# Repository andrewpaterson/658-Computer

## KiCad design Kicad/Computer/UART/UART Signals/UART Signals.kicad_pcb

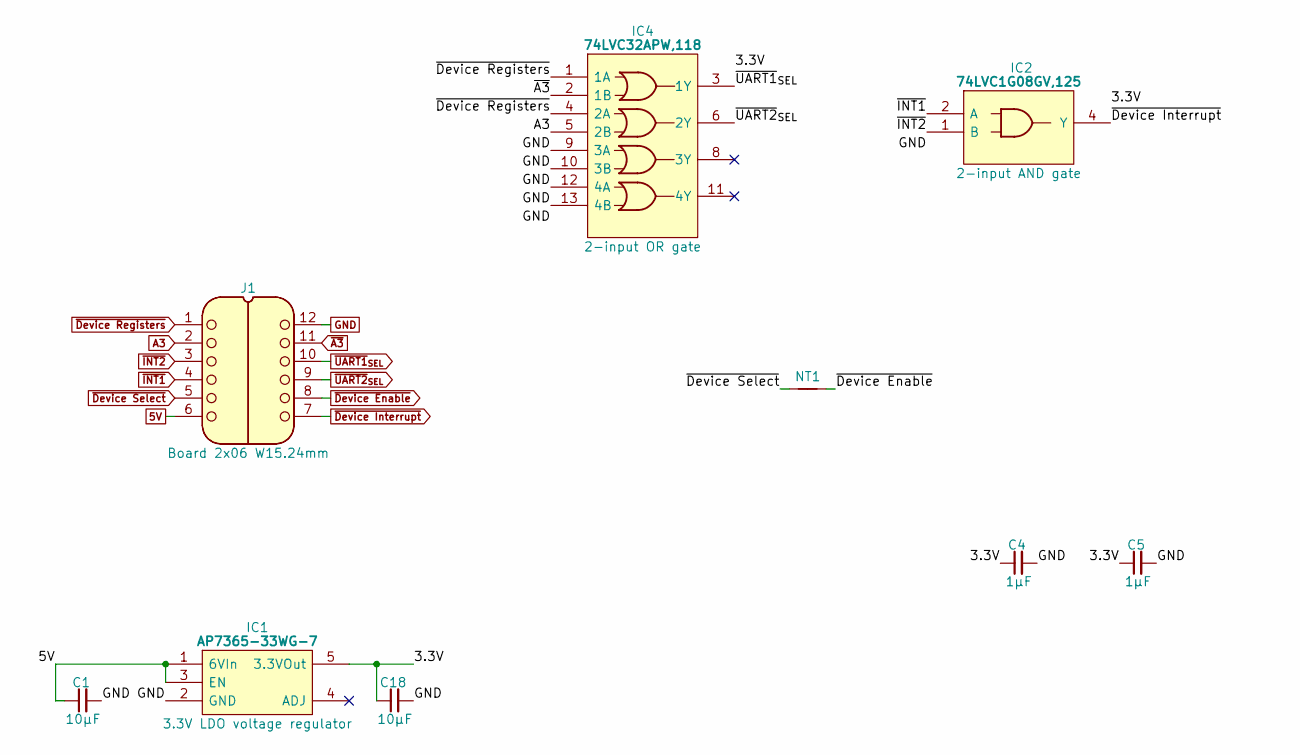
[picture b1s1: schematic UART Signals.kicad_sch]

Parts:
C1, C18: 10µF; C_0805
C4, C5: 1μF; C_0805
IC1: AP7365-33WG-7; SOT95P285X130-5N; Manufacturer_Part_Number AP7365-33WG-7; Mouser Part Number 621-AP7365-33WG-7
IC2: 74LVC1G08GV,125; SOT95P275X110-5N; Manufacturer_Part_Number 74LVC1G08GV,125; Mouser Part Number 771-74LVC1G08GV
IC4: 74LVC32APW,118; SOP65P640X110-14N; Manufacturer_Part_Number 74LVC32APW,118; Mouser Part Number 771-74LVC32APW-T
J1: Board 2x06 W15.24mm; DIP-12_Board_W15.24mm_Alt
NT1: NetTie; NetTie-2_SMD_Pad0.5mm

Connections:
5V: C1.1, IC1.1 (6VIn), IC1.3 (EN), J1.6
/3.3V: C4.1, C5.1, C18.1, IC1.5 (3.3VOut), IC2.5 (3V), IC4.14 (3V)
A3: IC4.5 (2B), J1.2
GND: C1.2, C4.2, C5.2, C18.2, IC1.2 (GND), IC2.3 (GND), IC4.7 (GND), IC4.9 (3A), IC4.10 (3B), IC4.12 (4A), IC4.13 (4B), J1.12
~A3: IC4.2 (1B), J1.11
~Device Enable: J1.8, NT1.2
~Device Interrupt: IC2.4 (Y), J1.7
~Device Registers: IC4.1 (1A), IC4.4 (2A), J1.1
~Device Select: J1.5, NT1.1
~INT1: IC2.2 (A), J1.4
~INT2: IC2.1 (B), J1.3
~UART1_{SEL}: IC4.3 (1Y), J1.10
~UART2_{SEL}: IC4.6 (2Y), J1.9

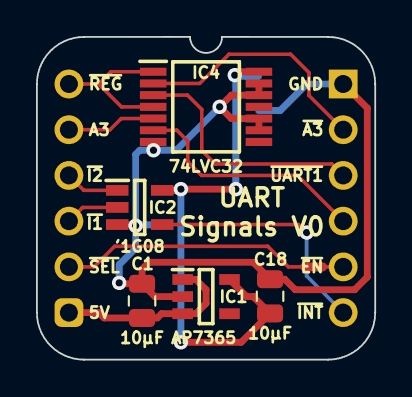
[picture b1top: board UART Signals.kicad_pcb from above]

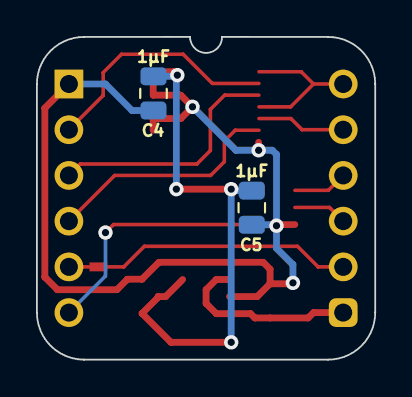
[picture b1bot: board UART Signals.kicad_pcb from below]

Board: 2 copper layers, 18.8 x 17.9 mm, 9 parts (2 on the bottom side), 13 nets.

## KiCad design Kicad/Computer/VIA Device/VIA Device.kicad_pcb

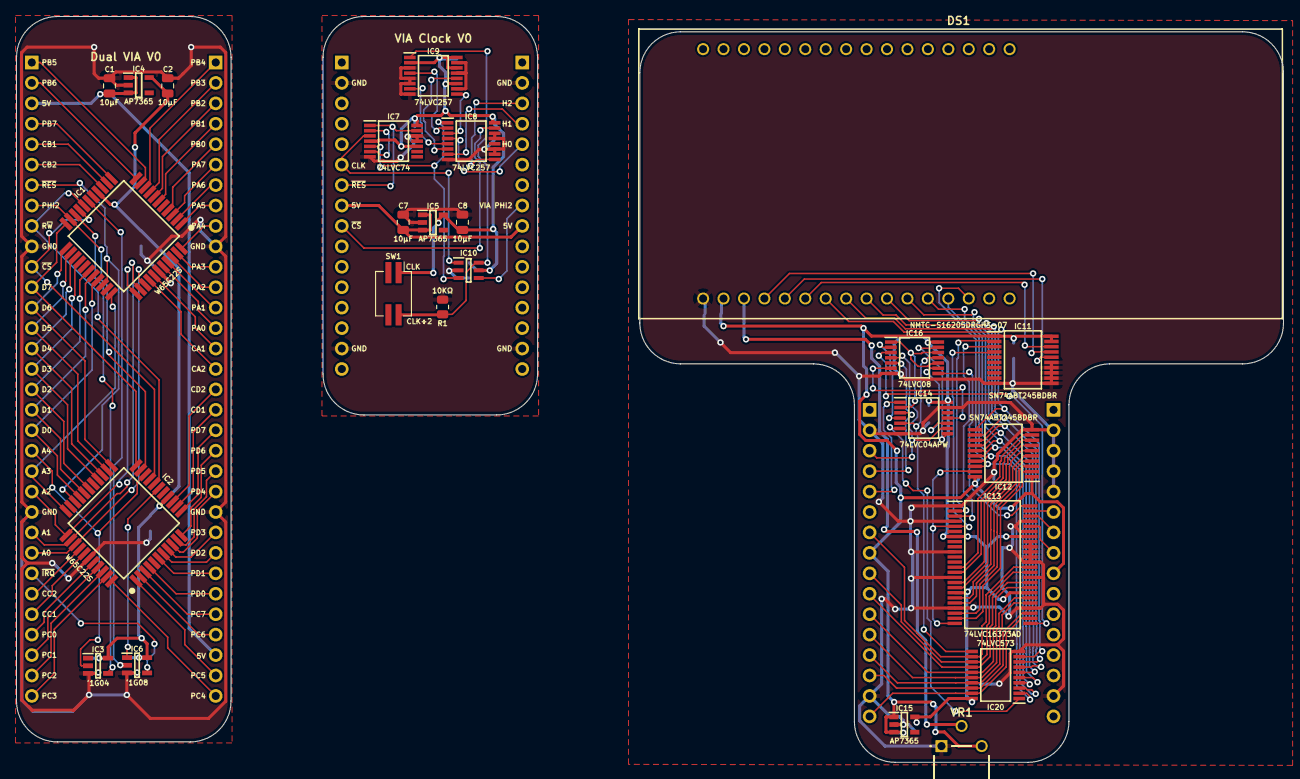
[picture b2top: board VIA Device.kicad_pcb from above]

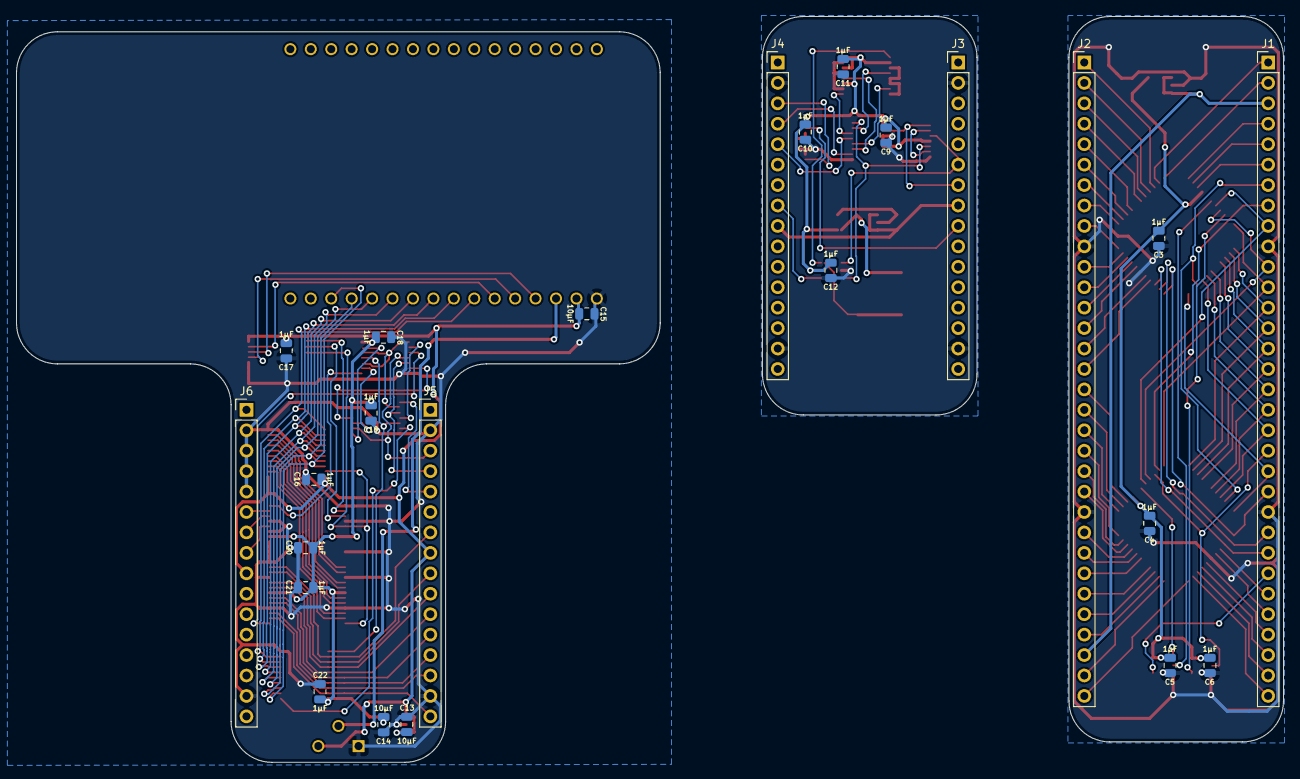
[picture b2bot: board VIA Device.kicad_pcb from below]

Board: 2 copper layers, 157.5 x 92.7 mm, 49 parts (24 on the bottom side), 130 nets.

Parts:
C1, C2, C7, C8, C13, C14, C15: 10μF; C_0805
C3, C4, C5, C6, C9, C10, C11, C12, C16, C17, C18, C19, C20, C21, C22: 1μF; C_0805
DS1: NMTC-S16205DRGHS-07; NMTCS16205DRGHS07_1
IC1, IC2: W65C22S6TQG-14; QFP80P1320X1320X270-44N
IC3: 74LVC1G04GV,125; SOT95P275X110-5N
IC4, IC5, IC15: AP7365-33WG-7; SOT95P285X130-5N
IC6: 74LVC1G08GV,125; SOT95P275X110-5N
IC7: 74LVC74APW,118; SOP65P640X110-14N
IC8, IC9: 74LVC257APW,118; SOP65P640X110-16N
IC10: 74LVC1G157GV-Q100H; SOT95P275X110-6N
IC11, IC12: SN74ABT245BDBR; SOP65P780X200-20N
IC13: 74LVC16373ADL,118; SOP64P1025X280-48N
IC14: 74LVC04APW,118; SOP65P640X110-14N
IC16: 74LVC08APW,112; SOP65P640X110-14N
IC20: 74LVC573APW,118; SOP65P640X110-20N
J1, J2: Conn_01x32_Pin; PinHeader_1x32_P2.54mm_Vertical
J3, J4, J5, J6: Conn_01x32_Pin; PinHeader_1x16_P2.54mm_Vertical
R1: 10KΩ; R_0805
SW1: SW_DIP_x02; SW_DIP_SPSTx02_Slide_KingTek_DSHP02TJ_W5.25mm_P1.27mm_JPin
VR1: 3306K-1-103; 3306K1103

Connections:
/Clock Control Board/1~Q: IC7.2 (1D), IC7.6 (~1Q)
/Clock Control Board/3.3V: C8.1, C9.1, C10.1, C11.1, C12.1, IC5.5 (VOUT), IC7.4 (~1SD), IC7.10 (~2SD), IC7.14 (3V), IC8.16 (3V), IC9.2 (1I0), IC9.11 (3I0), IC9.14 (4I0), IC9.16 (3V), IC10.5 (3V), SW1.1
/Clock Control Board/5V: C7.1, IC5.1 (VIN), IC5.3 (EN), J3.8, J4.9
/Clock Control Board/CH0_{OUT}: IC8.4 (1Y), J4.5
/Clock Control Board/CH1_{OUT}: IC8.7 (2Y), J4.4
/Clock Control Board/CH2_{OUT}: IC8.9 (3Y), J4.3
/Clock Control Board/CLK: IC7.3 (1CP), IC10.1 (I1), J3.6
/Clock Control Board/CLK÷2: IC7.5 (1Q), IC8.1 (S), IC10.3 (I0)
/Clock Control Board/GND: C7.2, C8.2, C9.2, C10.2, C11.2, C12.2, IC5.2 (GND), IC7.7 (GND), IC7.11 (2CP), IC7.12 (2D), IC8.8 (GND), IC8.10 (3I1), IC8.11 (3I0), IC8.13 (4I1), IC8.14 (4I0), IC9.3 (1I1), IC9.5 (2I0), IC9.6 (2I1), IC9.8 (GND), IC9.10 (3I1), IC9.13 (4I1), IC9.15 (~OE), IC10.2 (GND), J3.2, J3.15, J4.2, J4.15, R1.1
/Clock Control Board/Select CLK÷2: IC9.1 (S), IC10.6 (S), R1.2, SW1.4
/Clock Control Board/VIA PHI2 _{OUT}: IC10.4 (Y), J4.8
/Clock Control Board/~CS: IC8.15 (~OE), J3.9
/Clock Control Board/~Reset: IC7.1 (~1RD), IC7.13 (~2RD), J3.7
/LCD Display/3.3V: C14.1, C18.1, C19.1, C20.1, C21.1, C22.1, IC13.7 (3V), IC13.18 (3V), IC13.31 (3V), IC13.42 (3V), IC14.14 (3V), IC15.5 (VOUT), IC16.14 (3V), IC20.20 (3V)
/LCD Display/5V: C13.1, C15.1, C16.1, C17.1, DS1.2 (5V), IC11.1 (DIR), IC11.19 (~OE), IC11.20 (5V), IC12.1 (DIR), IC12.20 (5V), IC15.1 (VIN), IC15.3 (EN), J5.8, J6.9, VR1.3 (VIN)
/LCD Display/(RD+WD)·CS: IC13.48 (1LE), IC16.8 (3Y)
/LCD Display/A0: IC13.37 (1D7), J6.6
/LCD Display/A1: IC13.38 (1D6), J6.7
/LCD Display/A2: IC13.40 (1D5), J6.8
/LCD Display/CS: IC14.2 (1Y), IC16.1 (1A), IC16.10 (3B), IC16.12 (4A)
/LCD Display/D0: IC13.26 (2D7), IC20.12 (Q7), J5.7
/LCD Display/D0_{Latch}: IC12.2 (A0), IC13.23 (2Q7)
/LCD Display/D1: IC13.27 (2D6), IC20.13 (Q6), J5.9
/LCD Display/D1_{Latch}: IC12.3 (A1), IC13.22 (2Q6)
/LCD Display/D2: IC13.29 (2D5), IC20.14 (Q5), J5.10
/LCD Display/D2_{Latch}: IC12.4 (A2), IC13.20 (2Q5)
/LCD Display/D3: IC13.30 (2D4), IC20.15 (Q4), J5.11
/LCD Display/D3_{Latch}: IC12.5 (A3), IC13.19 (2Q4)
/LCD Display/D4: IC13.32 (2D3), IC20.16 (Q3), J5.12
/LCD Display/D4_{Latch}: IC12.6 (A4), IC13.17 (2Q3)
/LCD Display/D5: IC13.33 (2D2), IC20.17 (Q2), J5.13
/LCD Display/D5_{Latch}: IC12.7 (A5), IC13.16 (2Q2)
/LCD Display/D6: IC13.35 (2D1), IC20.18 (Q1), J5.14
/LCD Display/D6_{Latch}: IC12.8 (A6), IC13.14 (2Q1)
/LCD Display/D7: IC13.36 (2D0), IC20.19 (Q0), J5.16
/LCD Display/D7_{Latch}: IC12.9 (A7), IC13.13 (2Q0)
/LCD Display/DB0: DS1.7 (DB0), IC12.18 (B0), IC20.9 (D7)
/LCD Display/DB1: DS1.8 (DB1), IC12.17 (B1), IC20.8 (D6)
/LCD Display/DB2: DS1.9 (DB2), IC12.16 (B2), IC20.7 (D5)
/LCD Display/DB3: DS1.10 (DB3), IC12.15 (B3), IC20.6 (D4)
/LCD Display/DB4: DS1.11 (DB4), IC12.14 (B4), IC20.5 (D3)
/LCD Display/DB5: DS1.12 (DB5), IC12.13 (B5), IC20.4 (D2)
/LCD Display/DB6: DS1.13 (DB6), IC12.12 (B6), IC20.3 (D1)
/LCD Display/DB7: DS1.14 (DB7), IC12.11 (B7), IC20.2 (D0)
/LCD Display/E: DS1.6 (E), IC11.11 (B7)
/LCD Display/E_{Latch}: IC11.9 (A7), IC13.12 (1Q7)
/LCD Display/GND: C13.2, C14.2, C15.2, C16.2, C17.2, C18.2, C19.2, C20.2, C21.2, C22.2, DS1.1 (GND), IC11.10 (GND), IC11.14 (B4), IC11.15 (B3), IC11.16 (B2), IC11.17 (B1), IC11.18 (B0), IC12.10 (GND), IC13.1 (1~OE), IC13.4 (GND), IC13.10 (GND), IC13.15 (GND), IC13.21 (GND), IC13.28 (GND), IC13.34 (GND), IC13.39 (GND), IC13.41 (1D4), IC13.43 (1D3), IC13.44 (1D2), IC13.45 (GND), IC13.46 (1D1), IC13.47 (1D0), IC14.7 (GND), IC14.13 (6A), IC15.2 (GND), IC16.7 (GND), IC20.10 (GND), J5.2, J5.15, J6.2, J6.3, J6.4, J6.5, J6.15, VR1.1 (GND)
/LCD Display/RD: IC14.8 (4Y), IC16.13 (4B)
/LCD Display/RD+WD: IC14.10 (5Y), IC16.9 (3A)
/LCD Display/RD·CS: IC14.5 (3A), IC16.11 (4Y), IC20.11 (LE)
/LCD Display/RS: DS1.4 (RS), IC11.12 (B6)
/LCD Display/RS_{Latch}: IC11.8 (A6), IC13.11 (1Q6)
/LCD Display/R~W: DS1.5 (R/~W), IC11.13 (B5)
/LCD Display/R~W_{Latch}: IC11.7 (A5), IC12.19 (~OE), IC13.9 (1Q5), IC13.24 (2~OE)
/LCD Display/V_{0}: DS1.3 (V_{O}), VR1.2 (VOUT)
/LCD Display/WD: IC14.4 (2Y), IC16.2 (1B)
/LCD Display/WD·CS: IC13.25 (2LE), IC16.3 (1Y)
/LCD Display/~CS: IC14.1 (1A), J5.5
/LCD Display/~RD: IC14.9 (4A), IC16.4 (2A), J5.3
/LCD Display/~RD+~CS: IC14.6 (3Y), IC20.1 (~OE)
/LCD Display/~RD·~WD: IC14.11 (5A), IC16.6 (2Y)
/LCD Display/~WD: IC14.3 (2A), IC16.5 (2B), J5.4
/W65C22 Breakout Board/3.3V: C2.1, C3.1, C4.1, C5.1, C6.1, IC1.15 (5V), IC2.15 (5V), IC3.5 (3V), IC4.5 (VOUT), IC6.5 (3V)
/W65C22 Breakout Board/5V: C1.1, IC4.1 (VIN), IC4.3 (EN), J1.3, J2.30
/W65C22 Breakout Board/A0: IC1.36 (RS0), IC2.36 (RS0), J1.25
/W65C22 Breakout Board/A1: IC1.35 (RS1), IC2.35 (RS1), J1.24
/W65C22 Breakout Board/A2: IC1.34 (RS2), IC2.34 (RS2), J1.22
/W65C22 Breakout Board/A3: IC1.33 (RS3), IC2.33 (RS3), J1.21
/W65C22 Breakout Board/A4: IC2.20 (CS1), IC3.2 (A), J1.20
/W65C22 Breakout Board/CA1: IC1.38 (CA1), J2.15
/W65C22 Breakout Board/CA2: IC1.37 (CA2), J2.16
/W65C22 Breakout Board/CB1: IC1.13 (CB1), J1.5
/W65C22 Breakout Board/CB2: IC1.14 (CB2), J1.6
/W65C22 Breakout Board/CC1: IC2.38 (CA1), J1.28
/W65C22 Breakout Board/CC2: IC2.37 (CA2), J1.27
/W65C22 Breakout Board/CD1: IC2.13 (CB1), J2.18
/W65C22 Breakout Board/CD2: IC2.14 (CB2), J2.17
/W65C22 Breakout Board/D0: IC1.30 (D0), IC2.30 (D0), J1.19
/W65C22 Breakout Board/D1: IC1.29 (D1), IC2.29 (D1), J1.18
/W65C22 Breakout Board/D2: IC1.28 (D2), IC2.28 (D2), J1.17
/W65C22 Breakout Board/D3: IC1.26 (D3), IC2.26 (D3), J1.16
/W65C22 Breakout Board/D4: IC1.25 (D4), IC2.25 (D4), J1.15
/W65C22 Breakout Board/D5: IC1.24 (D5), IC2.24 (D5), J1.14
/W65C22 Breakout Board/D6: IC1.23 (D6), IC2.23 (D6), J1.13
/W65C22 Breakout Board/D7: IC1.22 (D7), IC2.22 (D7), J1.12
/W65C22 Breakout Board/GND: C1.2, C2.2, C3.2, C4.2, C5.2, C6.2, IC1.39 (GND), IC2.39 (GND), IC3.3 (GND), IC4.2 (GND), IC6.3 (GND), J1.10, J1.23, J2.10, J2.23
/W65C22 Breakout Board/PA0: IC1.40 (PA0), J2.14
/W65C22 Breakout Board/PA1: IC1.41 (PA1), J2.13
/W65C22 Breakout Board/PA2: IC1.42 (PA2), J2.12
/W65C22 Breakout Board/PA3: IC1.43 (PA3), J2.11
/W65C22 Breakout Board/PA4: IC1.44 (PA4), J2.9
/W65C22 Breakout Board/PA5: IC1.1 (PA5), J2.8
/W65C22 Breakout Board/PA6: IC1.2 (PA6), J2.7
/W65C22 Breakout Board/PA7: IC1.3 (PA7), J2.6
/W65C22 Breakout Board/PB0: IC1.4 (PB0), J2.5
/W65C22 Breakout Board/PB1: IC1.6 (PB1), J2.4
/W65C22 Breakout Board/PB2: IC1.7 (PB2), J2.3
/W65C22 Breakout Board/PB3: IC1.8 (PB3), J2.2
/W65C22 Breakout Board/PB4: IC1.9 (PB4), J2.1
/W65C22 Breakout Board/PB5: IC1.10 (PB5), J1.1
/W65C22 Breakout Board/PB6: IC1.11 (PB6), J1.2
/W65C22 Breakout Board/PB7: IC1.12 (PB7), J1.4
/W65C22 Breakout Board/PC0: IC2.40 (PA0), J1.29
/W65C22 Breakout Board/PC1: IC2.41 (PA1), J1.30
/W65C22 Breakout Board/PC2: IC2.42 (PA2), J1.31
/W65C22 Breakout Board/PC3: IC2.43 (PA3), J1.32
/W65C22 Breakout Board/PC4: IC2.44 (PA4), J2.32
/W65C22 Breakout Board/PC5: IC2.1 (PA5), J2.31
/W65C22 Breakout Board/PC6: IC2.2 (PA6), J2.29
/W65C22 Breakout Board/PC7: IC2.3 (PA7), J2.28
/W65C22 Breakout Board/PD0: IC2.4 (PB0), J2.27
/W65C22 Breakout Board/PD1: IC2.6 (PB1), J2.26
/W65C22 Breakout Board/PD2: IC2.7 (PB2), J2.25
/W65C22 Breakout Board/PD3: IC2.8 (PB3), J2.24
/W65C22 Breakout Board/PD4: IC2.9 (PB4), J2.22
/W65C22 Breakout Board/PD5: IC2.10 (PB5), J2.21
/W65C22 Breakout Board/PD6: IC2.11 (PB6), J2.20
/W65C22 Breakout Board/PD7: IC2.12 (PB7), J2.19
/W65C22 Breakout Board/PHI2: IC1.21 (PHI2), IC2.21 (PHI2), J1.8
/W65C22 Breakout Board/R~W: IC1.18 (R~W), IC2.18 (R~W), J1.9
/W65C22 Breakout Board/~A4: IC1.20 (CS1), IC3.4 (Y)
/W65C22 Breakout Board/~CS: IC1.19 (~CS2), IC2.19 (~CS2), J1.11
/W65C22 Breakout Board/~IRQ: IC6.4 (Y), J1.26
/W65C22 Breakout Board/~IRQ_{AB}: IC1.17 (~IRQ), IC6.2 (A)
/W65C22 Breakout Board/~IRQ_{CD}: IC2.17 (~IRQ), IC6.1 (B)
/W65C22 Breakout Board/~Reset: IC1.31 (~RES), IC2.31 (~RES), J1.7
unnamed: IC8.2 (1I0), IC9.4 (1Y)
unnamed: IC8.3 (1I1), IC9.9 (3Y)
unnamed: IC8.5 (2I0), IC9.7 (2Y)
unnamed: IC8.6 (2I1), IC9.12 (4Y)

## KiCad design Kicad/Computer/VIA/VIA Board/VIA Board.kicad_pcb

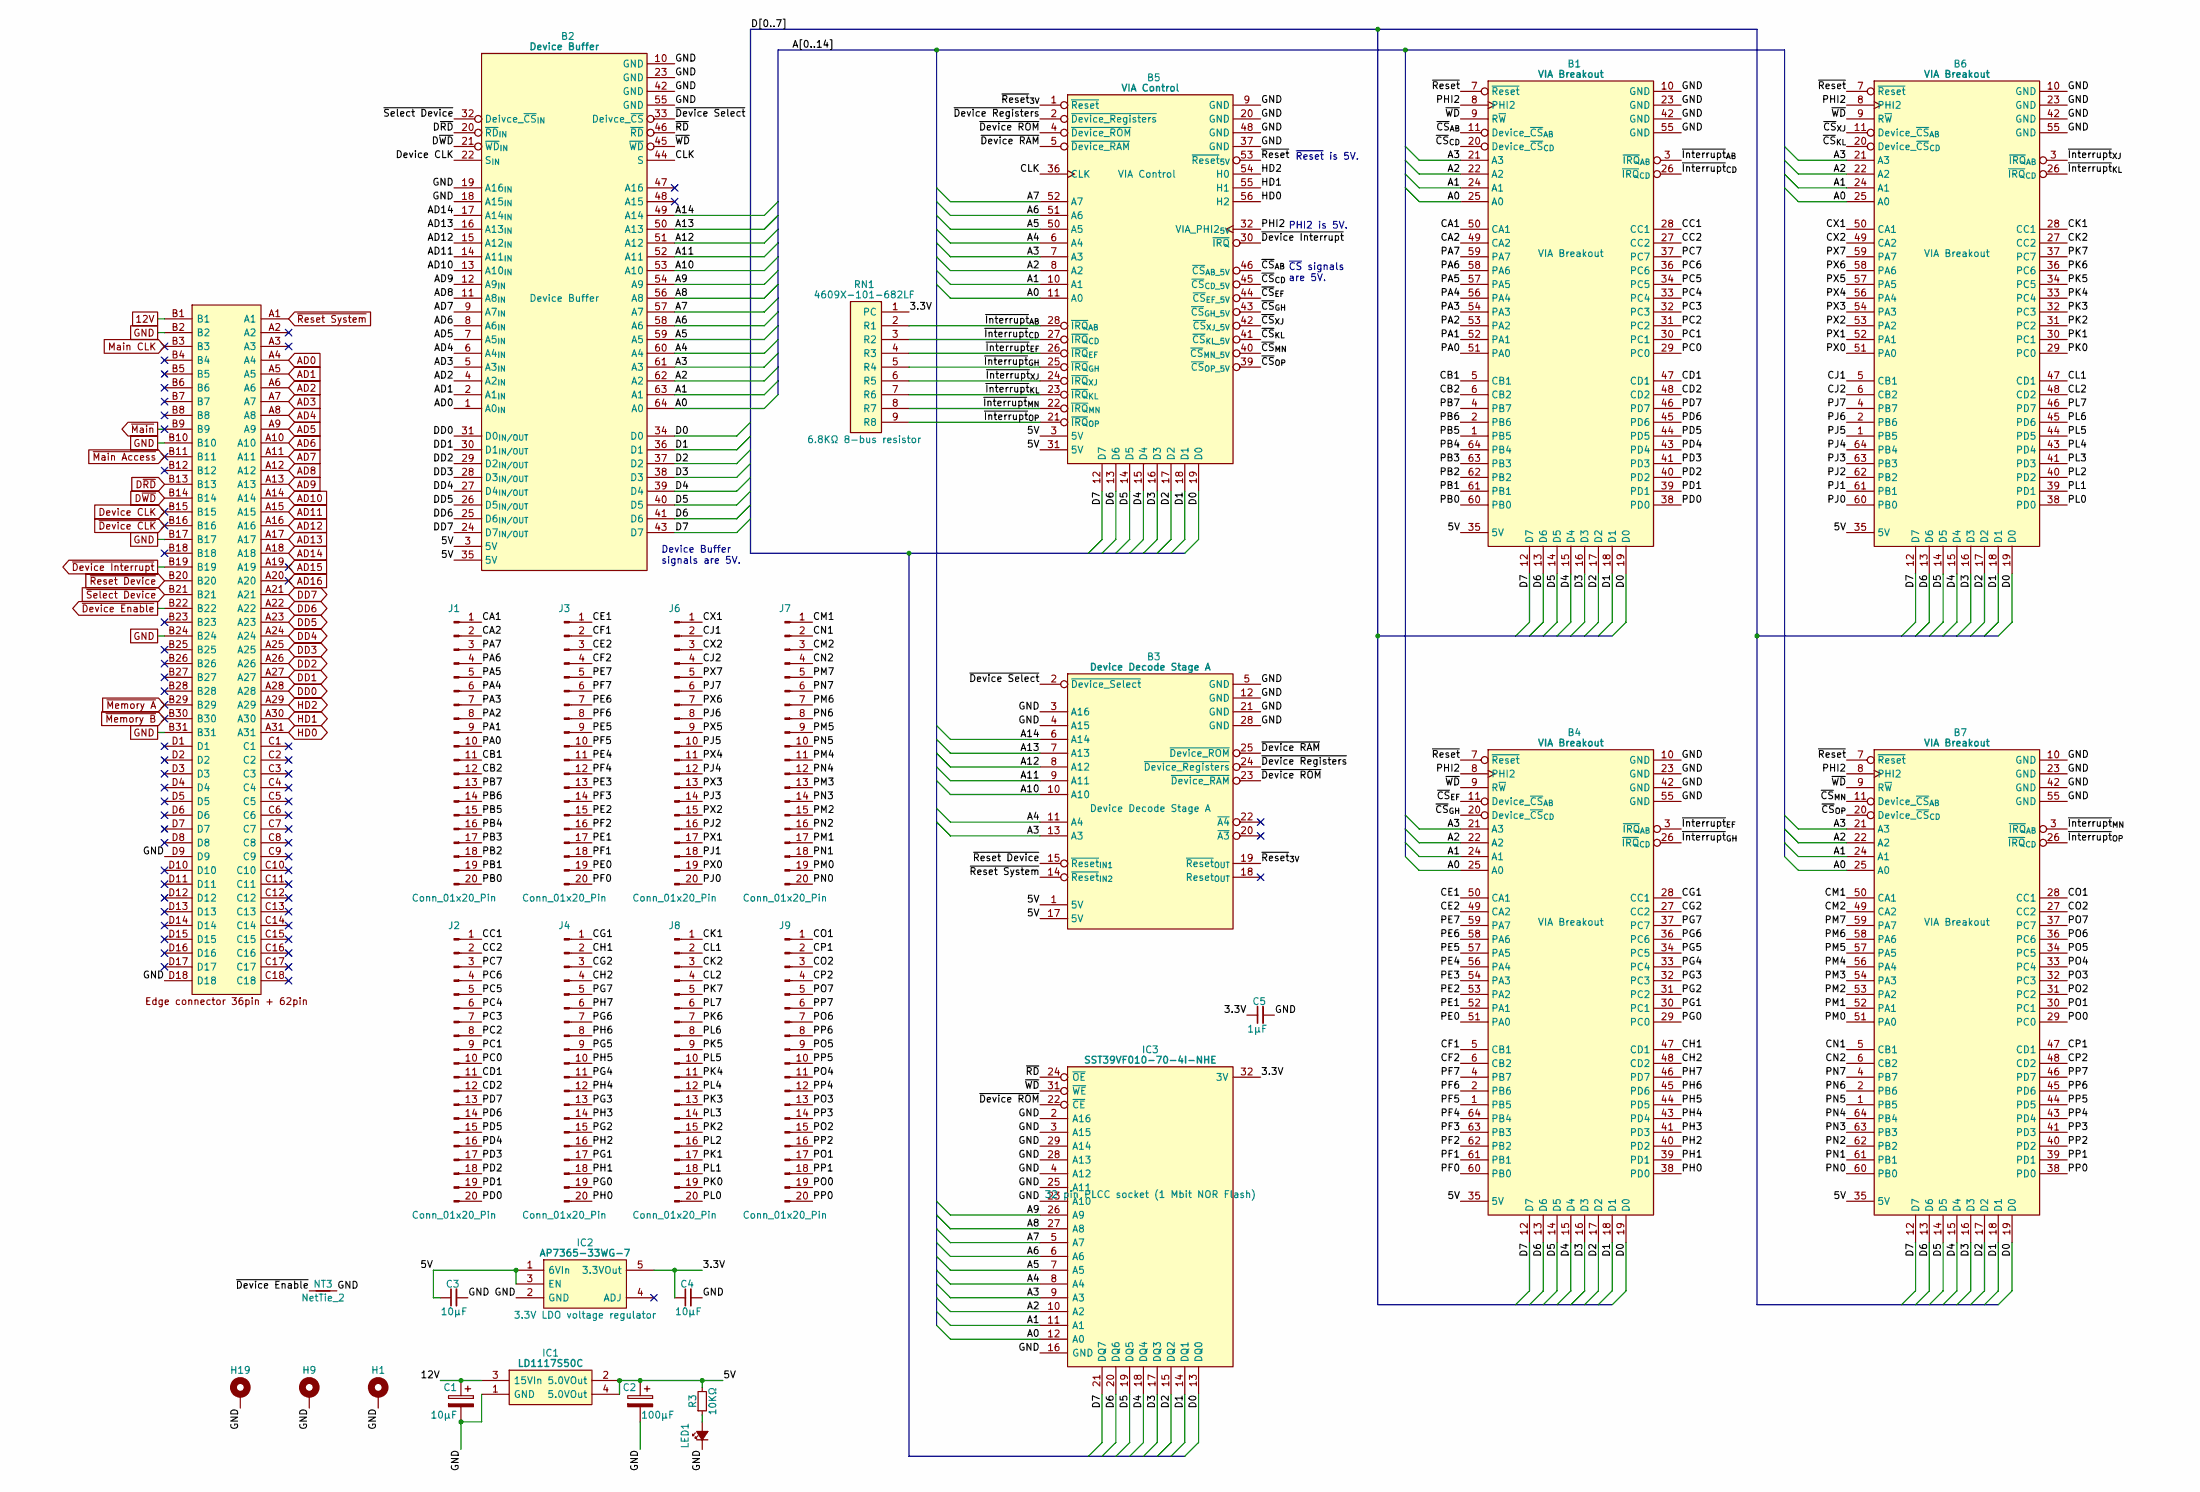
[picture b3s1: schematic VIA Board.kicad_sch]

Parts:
B1, B4, B6, B7: VIA Breakout; HCP65_VIA_Breakout
B2: Device Buffer; HCP65_Device_Buffer
B3: Device Decode Stage A; HCP65_Device_Decode_Stage_A
B5: VIA Control; HCP65_VIA_Control
C1: 10μF; CP_Radial_D4.0mm_P2.00mm
C2: 100μF; CP_Radial_D4.0mm_P2.00mm
C3, C4: 10µF; C_0805
C5: 1µF; C_0805
H1, H9, H19: MountingHole_Pad; HCP65_MountingHole_M3_
IC1: LD1117S50C; LD1117S33C; Manufacturer_Part_Number LD1117S50C
IC2: AP7365-33WG-7; SOT95P285X130-5N; Manufacturer_Part_Number AP7365-33WG-7; Mouser Part Number 621-AP7365-33WG-7
IC3: SST39VF010-70-4I-NHE; 5408803224008; Manufacturer_Part_Number SST39VF010-70-4I-NHE
J1, J2: Conn_01x20_Pin; PinHeader_1x20_P2.54mm_Horizontal
J3, J4, J6, J7, J8, J9: Conn_01x20_Pin; PinHeader_2x10_P2.54mm_Horizontal
J5: 395-098-520-350; 98pin Edge Connector; Manufacturer_Part_Number 395-098-520-350; Mouser Part Number 587-395-098-520-350
LED1: LED; LED_D5.0mm
NT3: NetTie_2; NetTie-2_SMD_Pad0.5mm
R3: 10KΩ; R_0805
RN1: 4609X-101-682LF; 4609X; Manufacturer_Part_Number 4609X-101-682LF; Mouser Part Number 652-4609X-1LF-6.8K

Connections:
12V: C1.1, IC1.3 (15VIn), J5.B1
/3.3V: C4.1, C5.1, IC2.5 (3.3VOut), IC3.32 (3V), RN1.1 (PC)
/5V: B1.35 (5V), B2.3 (5V), B2.35 (5V), B3.1 (5V), B3.17 (5V), B4.35 (5V), B5.3 (5V), B5.31 (5V), B6.35 (5V), B7.35 (5V), C2.1, C3.1, IC1.2 (5.0VOut), IC1.4 (5.0VOut), IC2.1 (6VIn), IC2.3 (EN), R3.2
/A0: B1.25 (A0), B2.64 (A0), B4.25 (A0), B5.11 (A0), B6.25 (A0), B7.25 (A0), IC3.12 (A0)
/A1: B1.24 (A1), B2.63 (A1), B4.24 (A1), B5.10 (A1), B6.24 (A1), B7.24 (A1), IC3.11 (A1)
/A2: B1.22 (A2), B2.62 (A2), B4.22 (A2), B5.8 (A2), B6.22 (A2), B7.22 (A2), IC3.10 (A2)
/A3: B1.21 (A3), B2.61 (A3), B3.13 (A3), B4.21 (A3), B5.7 (A3), B6.21 (A3), B7.21 (A3), IC3.9 (A3)
/A4: B2.60 (A4), B3.11 (A4), B5.6 (A4), IC3.8 (A4)
/A5: B2.59 (A5), B5.50 (A5), IC3.7 (A5)
/A6: B2.58 (A6), B5.51 (A6), IC3.6 (A6)
/A7: B2.57 (A7), B5.52 (A7), IC3.5 (A7)
/A8: B2.56 (A8), IC3.27 (A8)
/A9: B2.54 (A9), IC3.26 (A9)
/A10: B2.53 (A10), B3.10 (A10)
/A11: B2.52 (A11), B3.9 (A11)
/A12: B2.51 (A12), B3.8 (A12)
/A13: B2.50 (A13), B3.7 (A13)
/A14: B2.49 (A14), B3.6 (A14)
/CA1: B1.50 (CA1), J1.1
/CA2: B1.49 (CA2), J1.2
/CB1: B1.5 (CB1), J1.11
/CB2: B1.6 (CB2), J1.12
/CC1: B1.28 (CC1), J2.1
/CC2: B1.27 (CC2), J2.2
/CD1: B1.47 (CD1), J2.11
/CD2: B1.48 (CD2), J2.12
/CE1: B4.50 (CA1), J3.1
/CE2: B4.49 (CA2), J3.3
/CF1: B4.5 (CB1), J3.2
/CF2: B4.6 (CB2), J3.4
/CG1: B4.28 (CC1), J4.1
/CG2: B4.27 (CC2), J4.3
/CH1: B4.47 (CD1), J4.2
/CH2: B4.48 (CD2), J4.4
/CJ1: B6.5 (CB1), J6.2
/CJ2: B6.6 (CB2), J6.4
/CK1: B6.28 (CC1), J8.1
/CK2: B6.27 (CC2), J8.3
/CL1: B6.47 (CD1), J8.2
/CL2: B6.48 (CD2), J8.4
/CLK: B2.44 (S), B5.36 (CLK)
/CM1: B7.50 (CA1), J7.1
/CM2: B7.49 (CA2), J7.3
/CN1: B7.5 (CB1), J7.2
/CN2: B7.6 (CB2), J7.4
/CO1: B7.28 (CC1), J9.1
/CO2: B7.27 (CC2), J9.3
/CP1: B7.47 (CD1), J9.2
/CP2: B7.48 (CD2), J9.4
/CX1: B6.50 (CA1), J6.1
/CX2: B6.49 (CA2), J6.3
/D0: B1.19 (D0), B2.34 (D0), B4.19 (D0), B5.19 (D0), B6.19 (D0), B7.19 (D0), IC3.13 (DQ0)
/D1: B1.18 (D1), B2.36 (D1), B4.18 (D1), B5.18 (D1), B6.18 (D1), B7.18 (D1), IC3.14 (DQ1)
/D2: B1.17 (D2), B2.37 (D2), B4.17 (D2), B5.17 (D2), B6.17 (D2), B7.17 (D2), IC3.15 (DQ2)
/D3: B1.16 (D3), B2.38 (D3), B4.16 (D3), B5.16 (D3), B6.16 (D3), B7.16 (D3), IC3.17 (DQ3)
/D4: B1.15 (D4), B2.39 (D4), B4.15 (D4), B5.15 (D4), B6.15 (D4), B7.15 (D4), IC3.18 (DQ4)
/D5: B1.14 (D5), B2.40 (D5), B4.14 (D5), B5.14 (D5), B6.14 (D5), B7.14 (D5), IC3.19 (DQ5)
/D6: B1.13 (D6), B2.41 (D6), B4.13 (D6), B5.13 (D6), B6.13 (D6), B7.13 (D6), IC3.20 (DQ6)
/D7: B1.12 (D7), B2.43 (D7), B4.12 (D7), B5.12 (D7), B6.12 (D7), B7.12 (D7), IC3.21 (DQ7)
/PA0: B1.51 (PA0), J1.10
/PA1: B1.52 (PA1), J1.9
/PA2: B1.53 (PA2), J1.8
/PA3: B1.54 (PA3), J1.7
/PA4: B1.56 (PA4), J1.6
/PA5: B1.57 (PA5), J1.5
/PA6: B1.58 (PA6), J1.4
/PA7: B1.59 (PA7), J1.3
/PB0: B1.60 (PB0), J1.20
/PB1: B1.61 (PB1), J1.19
/PB2: B1.62 (PB2), J1.18
/PB3: B1.63 (PB3), J1.17
/PB4: B1.64 (PB4), J1.16
/PB5: B1.1 (PB5), J1.15
/PB6: B1.2 (PB6), J1.14
/PB7: B1.4 (PB7), J1.13
/PC0: B1.29 (PC0), J2.10
/PC1: B1.30 (PC1), J2.9
/PC2: B1.31 (PC2), J2.8
/PC3: B1.32 (PC3), J2.7
/PC4: B1.33 (PC4), J2.6
/PC5: B1.34 (PC5), J2.5
/PC6: B1.36 (PC6), J2.4
/PC7: B1.37 (PC7), J2.3
/PD0: B1.38 (PD0), J2.20
/PD1: B1.39 (PD1), J2.19
/PD2: B1.40 (PD2), J2.18
/PD3: B1.41 (PD3), J2.17
/PD4: B1.43 (PD4), J2.16
/PD5: B1.44 (PD5), J2.15
/PD6: B1.45 (PD6), J2.14
/PD7: B1.46 (PD7), J2.13
/PE0: B4.51 (PA0), J3.19
/PE1: B4.52 (PA1), J3.17
/PE2: B4.53 (PA2), J3.15
/PE3: B4.54 (PA3), J3.13
/PE4: B4.56 (PA4), J3.11
/PE5: B4.57 (PA5), J3.9
/PE6: B4.58 (PA6), J3.7
/PE7: B4.59 (PA7), J3.5
/PF0: B4.60 (PB0), J3.20
/PF1: B4.61 (PB1), J3.18
/PF2: B4.62 (PB2), J3.16
/PF3: B4.63 (PB3), J3.14
/PF4: B4.64 (PB4), J3.12
/PF5: B4.1 (PB5), J3.10
/PF6: B4.2 (PB6), J3.8
/PF7: B4.4 (PB7), J3.6
/PG0: B4.29 (PC0), J4.19
/PG1: B4.30 (PC1), J4.17
/PG2: B4.31 (PC2), J4.15
/PG3: B4.32 (PC3), J4.13
/PG4: B4.33 (PC4), J4.11
/PG5: B4.34 (PC5), J4.9
/PG6: B4.36 (PC6), J4.7
/PG7: B4.37 (PC7), J4.5
/PH0: B4.38 (PD0), J4.20
/PH1: B4.39 (PD1), J4.18
/PH2: B4.40 (PD2), J4.16
/PH3: B4.41 (PD3), J4.14
/PH4: B4.43 (PD4), J4.12
/PH5: B4.44 (PD5), J4.10
/PH6: B4.45 (PD6), J4.8
/PH7: B4.46 (PD7), J4.6
/PHI2: B1.8 (PHI2), B4.8 (PHI2), B5.32 (VIA_PHI2_{5V}), B6.8 (PHI2), B7.8 (PHI2)
/PJ0: B6.60 (PB0), J6.20
/PJ1: B6.61 (PB1), J6.18
/PJ2: B6.62 (PB2), J6.16
/PJ3: B6.63 (PB3), J6.14
/PJ4: B6.64 (PB4), J6.12
/PJ5: B6.1 (PB5), J6.10
/PJ6: B6.2 (PB6), J6.8
/PJ7: B6.4 (PB7), J6.6
/PK0: B6.29 (PC0), J8.19
/PK1: B6.30 (PC1), J8.17
/PK2: B6.31 (PC2), J8.15
/PK3: B6.32 (PC3), J8.13
/PK4: B6.33 (PC4), J8.11
/PK5: B6.34 (PC5), J8.9
/PK6: B6.36 (PC6), J8.7
/PK7: B6.37 (PC7), J8.5
/PL0: B6.38 (PD0), J8.20
/PL1: B6.39 (PD1), J8.18
/PL2: B6.40 (PD2), J8.16
/PL3: B6.41 (PD3), J8.14
/PL4: B6.43 (PD4), J8.12
/PL5: B6.44 (PD5), J8.10
/PL6: B6.45 (PD6), J8.8
/PL7: B6.46 (PD7), J8.6
/PM0: B7.51 (PA0), J7.19
/PM1: B7.52 (PA1), J7.17
/PM2: B7.53 (PA2), J7.15
/PM3: B7.54 (PA3), J7.13
/PM4: B7.56 (PA4), J7.11
/PM5: B7.57 (PA5), J7.9
/PM6: B7.58 (PA6), J7.7
/PM7: B7.59 (PA7), J7.5
/PN0: B7.60 (PB0), J7.20
/PN1: B7.61 (PB1), J7.18
/PN2: B7.62 (PB2), J7.16
/PN3: B7.63 (PB3), J7.14
/PN4: B7.64 (PB4), J7.12
/PN5: B7.1 (PB5), J7.10
/PN6: B7.2 (PB6), J7.8
/PN7: B7.4 (PB7), J7.6
/PO0: B7.29 (PC0), J9.19
/PO1: B7.30 (PC1), J9.17
/PO2: B7.31 (PC2), J9.15
/PO3: B7.32 (PC3), J9.13
/PO4: B7.33 (PC4), J9.11
/PO5: B7.34 (PC5), J9.9
/PO6: B7.36 (PC6), J9.7
/PO7: B7.37 (PC7), J9.5
/PP0: B7.38 (PD0), J9.20
/PP1: B7.39 (PD1), J9.18
/PP2: B7.40 (PD2), J9.16
/PP3: B7.41 (PD3), J9.14
/PP4: B7.43 (PD4), J9.12
/PP5: B7.44 (PD5), J9.10
/PP6: B7.45 (PD6), J9.8
/PP7: B7.46 (PD7), J9.6
/PX0: B6.51 (PA0), J6.19
/PX1: B6.52 (PA1), J6.17
/PX2: B6.53 (PA2), J6.15
/PX3: B6.54 (PA3), J6.13
/PX4: B6.56 (PA4), J6.11
/PX5: B6.57 (PA5), J6.9
/PX6: B6.58 (PA6), J6.7
/PX7: B6.59 (PA7), J6.5
/~CS_{AB}: B1.11 (Device_~CS_{AB}), B5.46 (~CS_{AB_5V})
/~CS_{CD}: B1.20 (Device_~CS_{CD}), B5.45 (~CS_{CD_5V})
/~CS_{EF}: B4.11 (Device_~CS_{AB}), B5.44 (~CS_{EF_5V})
/~CS_{GH}: B4.20 (Device_~CS_{CD}), B5.43 (~CS_{GH_5V})
/~CS_{KL}: B5.41 (~CS_{KL_5V}), B6.20 (Device_~CS_{CD})
/~CS_{MN}: B5.40 (~CS_{MN_5V}), B7.11 (Device_~CS_{AB})
/~CS_{OP}: B5.39 (~CS_{OP_5V}), B7.20 (Device_~CS_{CD})
/~CS_{XJ}: B5.42 (~CS_{XJ_5V}), B6.11 (Device_~CS_{AB})
/~Device RAM: B3.25 (~Device_ROM), B5.5 (~Device_RAM)
/~Device ROM: B3.23 (~Device_RAM), B5.4 (~Device_ROM), IC3.22 (~CE)
/~Device Registers: B3.24 (~Device_Registers), B5.2 (~Device_Registers)
/~Device Select: B2.33 (Deivce_~CS), B3.2 (~Device_Select)
/~Interrupt_{AB}: B1.3 (~IRQ_{AB}), B5.28 (~IRQ_{AB}), RN1.2 (R1)
/~Interrupt_{CD}: B1.26 (~IRQ_{CD}), B5.27 (~IRQ_{CD}), RN1.3 (R2)
/~Interrupt_{EF}: B4.3 (~IRQ_{AB}), B5.26 (~IRQ_{EF}), RN1.4 (R3)
/~Interrupt_{GH}: B4.26 (~IRQ_{CD}), B5.25 (~IRQ_{GH}), RN1.5 (R4)
/~Interrupt_{KL}: B5.23 (~IRQ_{KL}), B6.26 (~IRQ_{CD}), RN1.7 (R6)
/~Interrupt_{MN}: B5.22 (~IRQ_{MN}), B7.3 (~IRQ_{AB}), RN1.8 (R7)
/~Interrupt_{OP}: B5.21 (~IRQ_{OP}), B7.26 (~IRQ_{CD}), RN1.9 (R8)
/~Interrupt_{XJ}: B5.24 (~IRQ_{XJ}), B6.3 (~IRQ_{AB}), RN1.6 (R5)
/~RD: B2.46 (~RD), IC3.24 (~OE)
/~Reset: B1.7 (~Reset), B4.7 (~Reset), B5.53 (~Reset_{5V}), B6.7 (~Reset), B7.7 (~Reset)
/~Reset_{3V}: B3.19 (~Reset_{OUT}), B5.1 (~Reset)
/~WD: B1.9 (R~W), B2.45 (~WD), B4.9 (R~W), B6.9 (R~W), B7.9 (R~W), IC3.31 (~WE)
AD0: B2.1 (A0_{IN}), J5.A4
AD1: B2.2 (A1_{IN}), J5.A5
AD2: B2.4 (A2_{IN}), J5.A6
AD3: B2.5 (A3_{IN}), J5.A7
AD4: B2.6 (A4_{IN}), J5.A8
AD5: B2.7 (A5_{IN}), J5.A9
AD6: B2.8 (A6_{IN}), J5.A10
AD7: B2.9 (A7_{IN}), J5.A11
AD8: B2.11 (A8_{IN}), J5.A12
AD9: B2.12 (A9_{IN}), J5.A13
AD10: B2.13 (A10_{IN}), J5.A14
AD11: B2.14 (A11_{IN}), J5.A15
AD12: B2.15 (A12_{IN}), J5.A16
AD13: B2.16 (A13_{IN}), J5.A17
AD14: B2.17 (A14_{IN}), J5.A18
AD15: J5.A19
AD16: J5.A20
DD0: B2.31 (D0_{IN/OUT}), J5.A28
DD1: B2.30 (D1_{IN/OUT}), J5.A27
DD2: B2.29 (D2_{IN/OUT}), J5.A26
DD3: B2.28 (D3_{IN/OUT}), J5.A25
DD4: B2.27 (D4_{IN/OUT}), J5.A24
DD5: B2.26 (D5_{IN/OUT}), J5.A23
DD6: B2.25 (D6_{IN/OUT}), J5.A22
DD7: B2.24 (D7_{IN/OUT}), J5.A21
Device CLK: B2.22 (S_{IN}), J5.B15
D~RD: B2.20 (~RD_{IN}), J5.B13
D~WD: B2.21 (~WD_{IN}), J5.B14
GND: B1.10 (GND), B1.23 (GND), B1.42 (GND), B1.55 (GND), B2.10 (GND), B2.18 (A15_{IN}), B2.19 (A16_{IN}), B2.23 (GND), B2.42 (GND), B2.55 (GND), B3.3 (A16), B3.4 (A15), B3.5 (GND), B3.12 (GND), B3.21 (GND), B3.28 (GND), B4.10 (GND), B4.23 (GND), B4.42 (GND), B4.55 (GND), B5.9 (GND), B5.20 (GND), B5.37 (GND), B5.48 (GND), B6.10 (GND), B6.23 (GND), B6.42 (GND), B6.55 (GND), B7.10 (GND), B7.23 (GND), B7.42 (GND), B7.55 (GND), C1.2, C2.2, C3.2, C4.2, C5.2, H1.1 (GND), H9.1 (GND), H19.1 (GND), IC1.1 (GND), IC2.2 (GND), IC3.2 (A16), IC3.3 (A15), IC3.4 (A12), IC3.16 (GND), IC3.23 (A10), IC3.25 (A11), IC3.28 (A13), IC3.29 (A14), J5.B2, J5.B10, J5.B17, J5.B24, J5.B31, J5.D9, J5.D18, LED1.1 (K), NT3.2
HD0: B5.56 (H2), J5.A31
HD1: B5.55 (H1), J5.A30
HD2: B5.54 (H0), J5.A29
Main CLK: J5.B3
unnamed: LED1.2 (A), R3.1
~Device CLK: J5.B16
~Device Enable: J5.B22, NT3.1
~Device Interrupt: B5.30 (~IRQ), J5.B19
~Main Access: J5.B11
~Main: J5.B9
~Memory A: J5.B29
~Memory B: J5.B30
~Reset Device: B3.15 (~Reset_{IN1}), J5.B20
~Reset System: B3.14 (~Reset_{IN2}), J5.A1
~Select Device: B2.32 (Deivce_~CS_{IN}), J5.B21

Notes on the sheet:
Device Buffer signals are 5V.
~{CS} signals are 5V.
~{Reset} is 5V.
PHI2 is 5V.

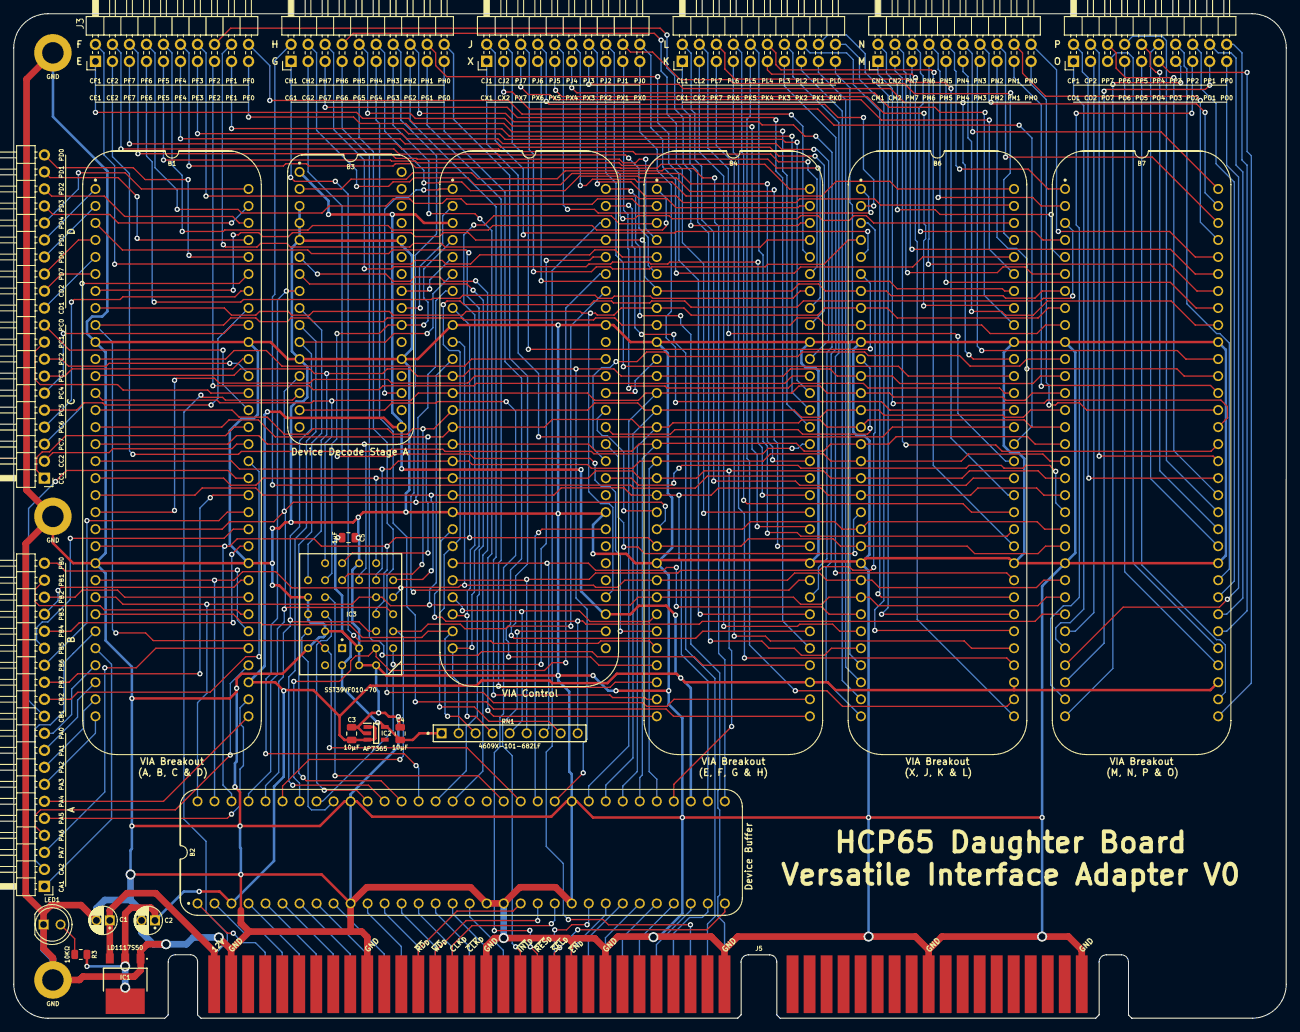
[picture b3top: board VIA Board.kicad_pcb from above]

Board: 2 copper layers, 190.0 x 150.0 mm, 31 parts (0 on the bottom side), 248 nets.

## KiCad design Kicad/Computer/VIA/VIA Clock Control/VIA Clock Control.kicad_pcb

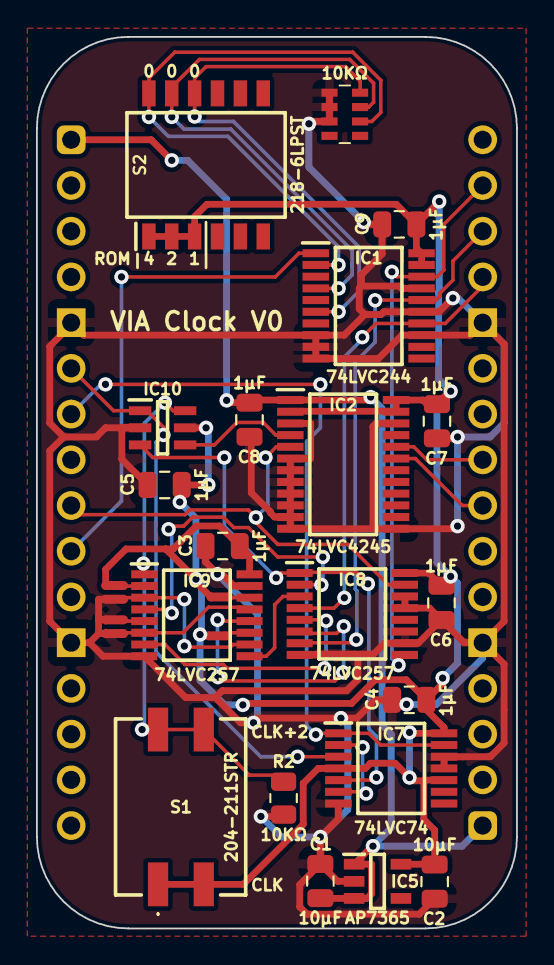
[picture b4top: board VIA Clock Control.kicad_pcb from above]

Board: 2 copper layers, 26.7 x 49.5 mm, 27 parts (0 on the bottom side), 29 nets.

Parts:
C1, C2: 10μF; C_0805
C3, C4, C5, C6, C7, C8, C9: 1μF; C_0805
IC1: 74LVC244APW,118; SOP65P640X110-20N
IC2: 74LVC4245APW,118; SOP65P640X110-24N
IC5: AP7365-33WG-7; SOT95P285X130-5N
IC7: 74LVC74APW,118; SOP65P640X110-14N
IC8, IC9: 74LVC257APW,118; SOP65P640X110-16N
IC10: 74LVC1G157GV-Q100H; SOT95P275X110-6N
J3: Conn_02x16_Counter_Clockwise; DIP-32_Board_W22.86mm
NT1, NT2, NT3, NT4, NT5, NT6: NetTie-2_SMD_Pad0.5mm
R2: 10KΩ; R_0805
RN1: CAY16-103J4LF; CAY16-J4
S1: 204-211STR; 204211STR
S2: 218-6LPST; SOIC127P844X265-12N

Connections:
/1~Q: IC7.2 (1D), IC7.6 (~1Q)
/3.3V: C2.1, C3.1, C4.1, C5.1, C6.1, C7.1, C9.1, IC1.19 (~2OE), IC1.20 (3V), IC2.2 (DIR), IC2.23 (3V), IC2.24 (3V), IC5.5 (VOUT), IC7.4 (~1SD), IC7.10 (~2SD), IC7.14 (3V), IC8.16 (3V), IC9.16 (3V), IC10.5 (3V), NT1.1, NT3.1, NT4.1, S1.C1, S1.C2, S2.1, S2.2, S2.3
/5V: C1.1, C8.1, IC2.1 (5V), IC5.1 (VIN), IC5.3 (EN), J3.1, J3.17
/CLK: IC7.3 (1CP), IC10.1 (I1), J3.6
/CLK÷2: IC7.5 (1Q), IC8.1 (S), IC10.3 (I0)
/CLK÷2 High H0: IC8.3 (1I1), IC9.9 (3Y)
/CLK÷2 High H1: IC8.6 (2I1), IC9.12 (4Y)
/CLK÷2 Low H0: IC8.2 (1I0), IC9.4 (1Y)
/CLK÷2 Low H1: IC8.5 (2I0), IC9.7 (2Y)
/GND: C1.2, C2.2, C3.2, C4.2, C5.2, C6.2, C7.2, C8.2, C9.2, IC1.8 (1A3), IC1.9 (2Y3), IC1.10 (GND), IC1.13 (2A2), IC1.15 (2A1), IC1.17 (2A0), IC2.3 (A0), IC2.6 (A3), IC2.7 (A4), IC2.8 (A5), IC2.9 (A6), IC2.10 (A7), IC2.11 (GND), IC2.12 (GND), IC2.13 (GND), IC2.22 (~OE), IC5.2 (GND), IC7.7 (GND), IC7.11 (2CP), IC7.12 (2D), IC8.8 (GND), IC8.10 (3I1), IC8.11 (3I0), IC8.13 (4I1), IC8.14 (4I0), IC9.8 (GND), IC9.15 (~OE), IC10.2 (GND), J3.5, J3.12, J3.21, J3.28, NT2.1, NT5.1, NT6.1, R2.1, RN1.1 (R1), RN1.2 (R2), RN1.3 (R3)
/H0: IC1.14 (1Y2), IC8.4 (1Y), J3.29
/H1: IC1.16 (1Y1), IC8.7 (2Y), J3.30
/H2: IC1.18 (1Y0), IC8.9 (3Y), J3.31
/ROM H0: IC1.6 (1A2), RN1.8 (R1), S2.10
/ROM H1: IC1.4 (1A1), RN1.7 (R2), S2.11
/ROM H2: IC1.2 (1A0), RN1.6 (R3), S2.12
/Select CLK H0: IC9.3 (1I1), IC9.10 (3I1), NT5.2
/Select CLK H1: IC9.6 (2I1), IC9.13 (4I1), NT6.2
/Select CLK÷2: IC9.1 (S), IC10.6 (S), R2.2, S1.N1, S1.N2
/Select CLK÷2 High H0: IC9.2 (1I0), NT1.2
/Select CLK÷2 High H1: IC9.5 (2I0), NT2.2
/Select CLK÷2 Low H0: IC9.11 (3I0), NT3.2
/Select CLK÷2 Low H1: IC9.14 (4I0), NT4.2
/VIA PHI2: IC2.4 (A1), IC10.4 (Y)
/VIA PHI2 _{OUT}: IC2.20 (B1), J3.25
/~Device ROM: IC1.1 (~1OE), J3.10
/~Device Registers: IC2.5 (A2), IC8.15 (~OE), J3.9
/~Reset: IC7.1 (~1RD), IC7.13 (~2RD), J3.7
/~VIA Select _{OUT}: IC2.19 (B2), J3.24
